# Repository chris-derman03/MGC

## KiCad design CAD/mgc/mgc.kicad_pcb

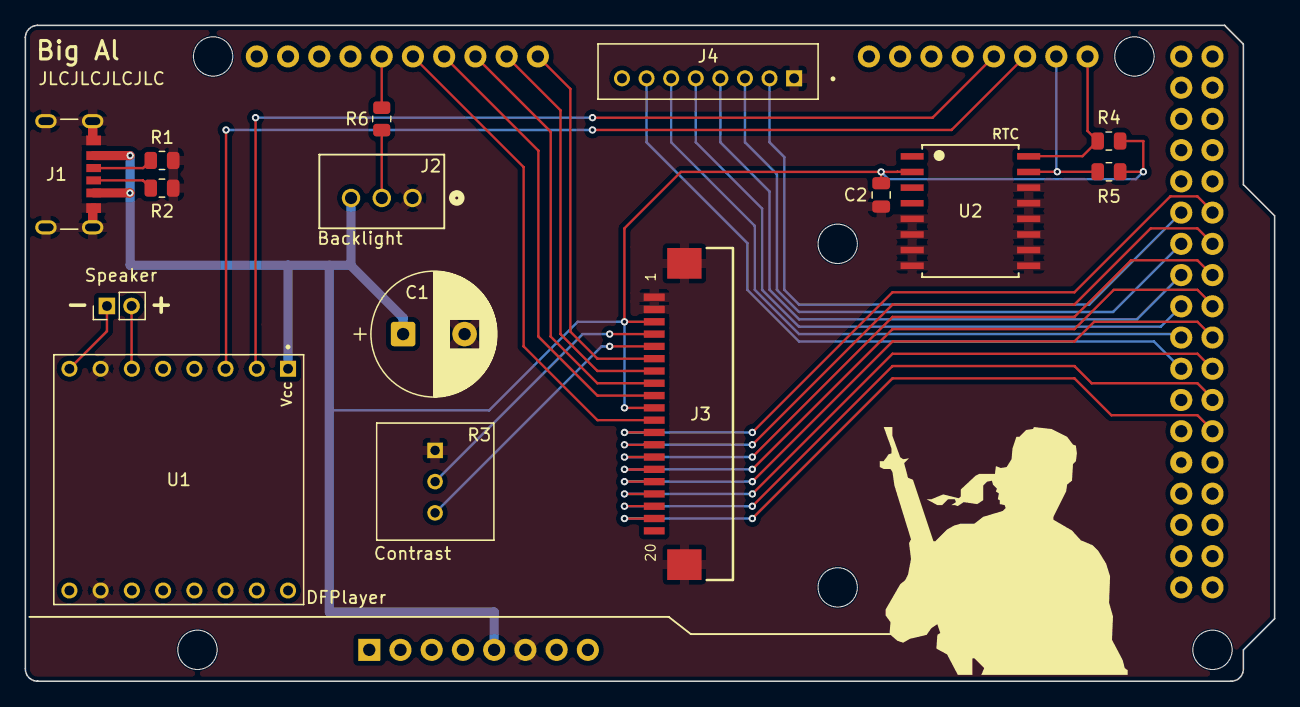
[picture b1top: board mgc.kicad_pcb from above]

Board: 2 copper layers, 101.6 x 53.3 mm, 16 parts (0 on the bottom side), 33 nets.

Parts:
A1: A000067; MODULE_A000067
C1: 1000u; CP_Radial_D10.0mm_P5.00mm
C2: 0.1uF; C_0805_2012Metric
J1: 10164359-00011LF; AMPHENOL_10164359-00011LF
J2: B3B-XH-A; CONN_B3B-XH-A_JST
J3: FFC3B07-20-T; GCT_FFC3B07-20-T
J4: B8B-PH-K-S; JST_B8B-PH-K-S
LS1: Speaker; PinHeader_1x02_P2.00mm_Vertical
R1, R2: 5.1k; R_0805_2012Metric
R3: Potentiometer; TRIM_COM-09806
R4, R5: 4.7k; R_0805_2012Metric
R6: 330; R_0805_2012Metric
U1: DFR0299; MODULE_DFR0299
U2: ds3231sn-; 21-0042B_16_MXM

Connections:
+5V: A1.5V_1 (+5V_1), C1.1, C2.2, J1.A9 (VBUS_A), J1.B9 (VBUS_B), J2.3, J3.3, J3.10, R4.1, R5.1, U1.1 (VCC), U2.2 (VCC)
/30 (TIME_SET): A1.30, J4.2
/31 (LCD_D0): A1.31, J3.12
/32 (HOUR++): A1.32, J4.3
/33 (LCD_D1): A1.33, J3.13
/34 (MINUTE++): A1.34, J4.4
/35 (LCD_D2): A1.35, J3.14
/36 (ALARM_SET): A1.36, J4.5
/37 (LCD_D3): A1.37, J3.15
/38 (ALARM_TOGGLE): A1.38, J4.6
/39 (LCD_D4): A1.39, J3.16
/40 (SNOOZE): A1.40, J4.7
/41 (LCD_D5): A1.41, J3.17
/43 (LCD_D6): A1.43, J3.18
/45 (LCD_D7): A1.45, J3.19
/*8 (LCD_WR): A1.8, J3.6
/*9 (LCD_RD): A1.9, J3.7
/*10 (LCD_CE): A1.10, J3.8
/*11 (LCD_C/D): A1.11, J3.9
/*12 (LCD_RESET): A1.12, J3.11
/*13 (Backlight): A1.13, R6.1
/Contrast Output: J3.5, R3.3
/Contrast Wiper: J3.4, R3.2
/RX1/19: A1.19, U1.3 (TX)
/SCL/21: A1.21, R4.2, U2.16 (SCL)
/SDA/20: A1.20, R5.2, U2.15 (SDA)
/TX1/18: A1.18, U1.2 (RX)
GND: A1.GND1, C1.2, C2.1, J1.A12 (GND_A), J1.B12 (GND_B), J1.SH1 (SHIELD), J1.SH2 (SHIELD__1), J1.SH3 (SHIELD__2), J1.SH4 (SHIELD__3), J2.1, J3.1, J3.2, J3.S1 (SHIELD), J3.S2 (SHIELD), J4.1, R1.1, R2.2, R3.1, U1.7 (GND), U1.10 (GND__1), U2.5 (NC), U2.6 (NC), U2.7 (NC), U2.8 (NC), U2.9 (NC), U2.10 (NC), U2.11 (NC), U2.12 (NC), U2.13 (GND), U2.14 (VBAT)
unnamed: J1.A5 (CC1), R1.2
unnamed: J1.B5 (CC2), R2.1
unnamed: J2.2, R6.2
unnamed: LS1.2, U1.6 (SPK1)
unnamed: LS1.1, U1.8 (SPK2)

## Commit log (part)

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2026-06-01 The screen turns on
2026-06-02 Bug Fix: initialize_display()
2026-06-04 Clock Logic. RTC Interface.
2026-06-04 Clock logic displays
2026-06-04 Physical Clock Interface added. Alarm functionality.
